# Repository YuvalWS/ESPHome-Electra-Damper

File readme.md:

# ESPHome Electra Damper

## Why?
The AC units in my rooms have electric dampers that are controlled by an IR remote. I wanted to automate them using Home Assistant.

The easy approach is to use a smart IR controller (for example, Broadlink) and record the open/close commands. This solution has some disadvantages:

1. It's less fun.
2. It requires a spot with a direct line of sight to the IR receiver.
3. It requires a permanent power source.
4. It has no feedback - if something interrupts the line of sight, I won't know whether the command worked.

## Reversing the controller
I started by disassembling the controller and examining the circuit. This is what I found.

<table>
  <tr>
    <td align="center">
      
      <div>Controller case</div>
    </td>
    <td align="center">
      
      <div>Controller front</div>
    </td>
    <td align="center">
      
      <div>Controller back</div>
    </td>
  </tr>
</table>

- It has four wires and two LEDs (green and red) that indicate state.
- The wires terminate in a **JST PH 4-pin connector (2.0 mm pitch)**, so the controller can be unplugged from the damper unit without cutting anything. Any JST PH 2.0 4-pin pigtail will mate with it.
- It has a physical toggle button, which is great because I don't have to reverse-engineer the IR protocol - I can just emulate the button press.
- I tried feeding the pictures to some AI tools, but they were not helpful and provided incorrect answers.

I didn't have enough knowledge to inspect the circuit further, so I turned to the only diagnostic tool I'm familiar with: a multimeter. I reconnected the controller and started measuring voltages.

- I identified the yellow wire as VCC (12 V) and the green wire as GND.
- There were two other wires. I assumed one was a state/input line and the other was the control line.
- The black wire measured ≈12 V at idle and dropped to ≈2.5 V when I pressed the button to open the damper, each press changes the voltage again - this is the state line.
- The red wire measured ≈5 V at idle and briefly dropped to about 1–2 V when the button was pressed. I looked this up and determined it behaves like an active-low (pull-down) control line.
### Reversing summary

| Wire   | Function                                    |
|--------|---------------------------------------------|
| Yellow | VCC (12 V)                                  |
| Green  | GND                                         |
| Black  | State (≈2.5 V when open, ≈12 V when closed) |
| Red    | Control (active-low, ≈5 V idle)             |

Connector: **JST PH 2.0 mm, 4 pins** (male header on the damper side, female housing on the controller pigtail).

## Building the smart damper
I decided to use an ESP32 board because it has a beginner-friendly workflow (ESPHome with ESPHome Builder) and an easy-to-use Home Assistant integration.
### VCC
The original controller uses a 12 V input, but ESP32 boards expect 5 V or 3.3 V. I used a DC buck converter to step the voltage down.

### State
The state voltage presented a challenge because ESP GPIO pins are limited to 3.3 V. I considered using an optocoupler to fully isolate the circuits, but I realized a 2.5 V "low" might still be enough to partially turn on an optocoupler LED, which would make detection unreliable.

Instead, I used a simple voltage divider with 10 kΩ and 3.3 kΩ resistors. This scales the ~2.5–12 V range down to roughly 0.6–3.0 V, which is safe for the ESP. This range is prefect for the default GPIO LOW\HIGH detection.

### Control
The simplest way to emulate the pull-down switch is with a transistor that connects the line to ground when activated. I used a 2N3904 NPN transistor: collector to the red wire, emitter to GND, and the base connected to a GPIO pin through a 1 kΩ resistor to protect the GPIO pin.

<div style="display: grid; grid-template-columns: minmax(auto, 800px); justify-content: center; margin: 2rem 0;">
  <figure style="margin: 0; text-align: center;">
    
    <figcaption>ESP wiring (conceptual)</figcaption>
  </figure>
</div>

## ESPHome configuration

### Project Structure
The configuration is split with ESPHome's **packages** feature, so the damper logic can be reused on any board:

```
├── common.yaml         # Shared: WiFi, API, OTA, captive portal, web server, time
├── damper_package.yaml # Damper control logic (reusable, pins via substitutions)
├── damper.yaml         # Standalone ESP32-S3 config with built-in RGB LED
├── damper_board.yaml   # ESP32-C3 SuperMini on the PCB in hardware/
├── hardware/           # PCB (Gerbers, generator script) and 3D-printed case
└── secrets.yaml        # Credentials (gitignored)
```

**Benefits:**
- Reuse the damper logic across multiple devices
- Update WiFi credentials in one place (`common.yaml`)
- Easy to create new combinations (e.g. the same damper on a different board, or with extra sensors)

### Pin Configuration
`damper_package.yaml` takes its pins from substitutions, so adapting to another ESP32 board only means changing the `substitutions` block in the device YAML:

```yaml
substitutions:
  damper_trigger_pin: "GPIO0"  # Damper control output (transistor base)
  damper_state_pin: "GPIO2"    # Damper state input (via voltage divider)

packages:
  common: !include common.yaml
  damper: !include damper_package.yaml
```

**⚠️ Strapping pins:** GPIO2 (and GPIO8/GPIO9) are strapping pins on ESP32-C3. If the board fails to boot with the damper connected, move `damper_state_pin` to a non-strapping pin (GPIO1, GPIO3, GPIO4, GPIO5, ...).

### Compiling and Flashing

**Prerequisites:**
```bash
pip install esphome
```

**Compile locally:**
```bash
esphome compile damper.yaml
```

**Flash via USB:**
```bash
esphome upload damper.yaml
```

Or manually with esptool:
```bash
esptool.py write_flash 0x0 .esphome/build/damper/.pioenvs/damper/firmware.factory.bin
```

**OTA update (after initial flash):**
```bash
esphome upload damper.yaml --device damper.local
```

Or use Home Assistant's ESPHome integration for OTA updates.

### Configuration Details
I implemented the transistor as an internal switch (no direct user control). A template button simulates the original controller's button press by turning the internal switch on for 200ms, allowing current to flow into the transistor base and actuating the pull-down. The button entity is exposed to Home Assistant to mimic the physical controller button.

A sensor reports the damper state; this is also reflected physically by the built-in RGB LED.

A template switch serves as the primary user interface for the damper. Its state is derived from the sensor so it reliably represents the actual damper position, and toggling the switch triggers the template button to change the damper state.

[Full ESPHome builder configuration yaml](damper.yaml)

<div style="display: grid; grid-template-columns: minmax(auto, 600px); justify-content: center; margin: 2rem 0;">
  <figure style="margin: 0; text-align: center;">
    
    <figcaption>Home Assistant view</figcaption>
  </figure>
</div>

## PCB and case
The perfboard prototype has a PCB and a printed wall case that can be aimed up/down and left/right in [hardware/](hardware/README.md). The board isolates the damper's wires from the ESP with optocouplers, takes a socketed ESP32-C3 SuperMini and an LD2410 presence radar, and has a jumper to choose between the damper's 12 V, an external 5 V supply, or USB. All the measurements taken on the damper's cable are recorded there.

## TODO
* Replace the ESP32-S3 with a smaller ESP module (like the ESP-Super-Mini), use a compact buck converter, and fit everything into a small tidy case. This will require using an external LED indicator instead of the ESP32-S3's built-in LED.
* Build and test the PCB in `hardware/` (designed, not yet manufactured).
* For a network-failure-proof solution, keep a physical button like the original control or add an IR receiver to support the original remote.
* I might use the fact that I already have a powered ESP32 in a strategic spot and connect additional sensors (temperature, light, or presence).

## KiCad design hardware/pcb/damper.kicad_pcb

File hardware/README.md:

# Damper controller hardware: PCB and two-axis wall case

Rev 1. A 61 x 71 mm two-layer, all through-hole board for a socketed ESP32-C3 SuperMini and an LD2410 radar, and a printed case whose wall mount aims it up/down and left/right.

Nothing here has been built yet. The board passes KiCad's design-rule check and the firmware config validates, but no board has been made, no part printed, and the two optocoupler stages have not been tried against a real damper.

## Do not order before these checks

| # | Check | Why |
|---|-------|-----|
| 1 | Build the control and state stages (see Circuit) on a breadboard and try them on the damper | They replace the divider and bare transistor that are known to work. Component values come from the measurements below, not from a test. |
| 2 | Print `pcb/damper-1to1.pdf` at 100 % and press the real SuperMini, LD2410, JST header, regulator and screw terminal onto the paper | Footprints come from KiCad's library and from caliper photos, not from parts in hand. |
| 3 | Read the pin names printed on your LD2410C and compare with J7: TX, RX, OUT, GND, VCC from the top | The order matches Hi-Link's data sheet (V1.00, table 1), but clones differ. If it is reversed the module still fits: it then lies to the other side of J7. If it is different, edit `RADAR_C` in `pcb/gen_pcb.py`. |
| 4 | With the board bare, plug the wall cable into J1 and confirm yellow lands on the pin marked Y | Yellow = pin 1 was read from a photo of the original board. |
| 5 | Measure the height of the SuperMini's USB-C socket above the PCB once it sits in its sockets | `usb_z` and `stack_h` in `case/case.scad` assume 13.6 mm and 18 mm. |

## Review, 19 November 2026

An outside review of this branch raised three points. Results of checking each:

| Point | Result |
|-------|--------|
| The board file at commit `ba88094` has three copper defects (a CTRL track through pad D3.2, pad JP2.2 cut off from GND, JP2.2 overlapping D2.1) and the Gerber ZIP is an older layout | Not a fault in the board; it is how the review read the file. The review's file hashes match `ba88094`, and the ZIP's copper, mask, silkscreen, outline and drill files are identical to a fresh KiCad export of that same file. All three defects sit on D3 and JP2, the only footprints turned 90 degrees, and they reproduce exactly when the 90-degree rotation is applied with the wrong sign: KiCad's y axis points down, so the y-up rotation formula mirrors the pads. With that error, D3.2 lands 0.254 mm from the CTRL track (the review's own figure; it is really 6.35 mm away), and JP2.2 lands 1.8 mm from D2.1, inside the damper-side pour. KiCad's design-rule check finds no shorts or unconnected nets, and a separate script that tests every pad against every pad and track of another net finds no conflicts. Regenerating from `gen_pcb.py` is safe; tools that read `.kicad_pcb` files directly must apply footprint rotation clockwise. |
| The radar is fed through D1, below its advised 5 V | Confirmed and fixed. D1 now feeds only the ESP's 5V pin; the radar sits on the rail ahead of it (see Power select). |
| The 200 mA isolated converter U4 cannot supply the radar | Confirmed. Hi-Link asks for more than 200 mA of supply capacity for the LD2410C. U4 is now marked for boards without the radar. |

## Measurements

Taken on the wall cable with the original controller unplugged, unless noted. Same results in two rooms.

### Connector

JST PH, 2.0 mm pitch, 4 positions. Female housing on the wall cable, male header on the controller.

| Pin | Wire | Function |
|-----|------|----------|
| 1 | Yellow | 12 V |
| 2 | Green | GND |
| 3 | Red | Control, pulled low to toggle |
| 4 | Black | State |

Order as seen with the housing's key facing you, left to right: yellow, green, red, black. On the original board yellow sits on the square pad. A bought JST PH pigtail may use other colours (the one used for measuring has white in place of green).

### Voltages

| Line | Condition | Open circuit | With 10 k to GND |
|------|-----------|--------------|------------------|
| Red (control) | idle | 5.15 V | 5.10 V |
| Black (state) | damper closed | 12.07 V | 11.95 V |
| Black (state) | damper open | 0 V | 0 V |
| Black (state) | damper open, original controller connected | 2.5 V | - |
| Yellow (12 V) | no load | 12.09 V | 11.97 V |
| Yellow (12 V) | powering the ESP32-S3 (N16R8 dev board) through a buck converter | 11.55 V | - |

What they say:

- **Control** has about 100 ohm behind it, so pulling it low takes tens of mA. The original button pulls it to 1-2 V, not to 0.
- **State** is stiff at 12 V when closed. When open it reads 0 V on a bare cable and 2.5 V with the original controller attached, so the 2.5 V comes from the controller's own circuit. The detector's threshold of about 6 V handles both.
- **12 V** drops 0.54 V under an ESP32-S3. It can power the board, but there is not much to spare.

Short-circuit currents were also read with the meter on its 20 mA range: red to green 0, black to green 0, yellow to green 0.83 mA. They contradict the voltage readings above and are not used. Do not repeat them: shorting the 12 V line through a meter is a dead short.

### Parts

| Part | Measured |
|------|----------|
| ESP32-C3 SuperMini (HW-466AB) | about 18 x 22.5 mm, two rows of 8 pins |
| HLK-LD2410C V1.1 | about 16 mm across the edge with the 5-pin 2.54 mm header |
| HLK-LD2410B | about 7 mm wide, five 1.27 mm pads on one short end |

Read from caliper photos, good to about half a millimetre.

## Files

| File | What it is |
|------|------------|
| `pcb/gerbers/damper-rev1.zip` | Gerbers and drill files. Upload to PCBWay: 2 layers, 1.6 mm, any colour, lead-free HASL. `source.txt` inside records the SHA-256 of the `damper.kicad_pcb` they were exported from. |
| `pcb/damper.kicad_pcb` | The board, opens in KiCad 9 or newer. |
| `pcb/gen_pcb.py` | Generates the board. There is no schematic; the netlist is the part tables in this script, and it routes the tracks itself. |
| `pcb/export.ps1` | Runs the generator, the design-rule check, and writes the Gerbers and the PDF. |
| `pcb/damper-1to1.pdf` | Pads, silkscreen and outline at 1:1 for the paper check. |
| `pcb/bom.csv` | Parts list, written by the generator. |
| `case/case.scad` | Parametric case (OpenSCAD). |
| `case/body.stl`, `cover.stl`, `swing-plate.stl`, `wall-plate.stl` | Printable parts, already in print orientation. |
| `case/case-ball.scad` | The same case on a ball-joint mount. Includes `case.scad`. |
| `case/body-ball.stl`, `cover-ball.stl`, `ball-stalk.stl`, `ball-base.stl`, `tripod-adapter.stl` | Printable parts for the ball-joint version. |
| `../damper_board.yaml` | ESPHome config for this board. |

After editing `gen_pcb.py`:

```
pwsh hardware/pcb/export.ps1
```

The design-rule check in that script ignores courtyard overlaps: the axial resistors sit on a 2.54 mm pitch, closer than KiCad's courtyards allow, which is tight but fits 1/4 W parts.

## Circuit

Two grounds: `AC_GND` on the damper side (bottom-left block of the board, outlined on the silkscreen) and `GND` on the ESP side. Only U1, U2, the regulator and the jumper JP2 cross the 1 mm gap between them.

```
 DAMPER SIDE (AC_GND)                    |  ESP SIDE (GND)
                                         |
 12V --F1 PTC--D2 1N5819--+--C1 100uF    |
                 D3 TVS 15V to AC_GND    |
                          +--> U3 or U4 --> 5V_REG
                                         |
 12V --R5 4k7--> U1 collector            |  GPIO0 --R1 220R--> U1 LED --> GND
 U1 emitter --+-- Q2 base, R6 10k to AC_GND
 CTRL (red) --R7 33R-- Q2 collector      |
              Q2 emitter -> AC_GND       |
                                         |
 STATE (black) --ZD1 5V1--R8 10k--+-- Q1 base, R9 10k to AC_GND
 12V --R10 2k2--> U2 LED --> Q1 collector|  3V3 --R2 10k--+-- GPIO1
                  Q1 emitter -> AC_GND   |                U2 collector, emitter GND
```

- **Control:** the optocoupler U1 turns on Q2, which pulls the red wire down through R7. 33 ohm limits the current to about 40 mA and leaves the line near 1.3 V, like the original button. If the damper does not react, replace R7 with a wire link; that is what the prototype's transistor does.
- **State:** the zener sets a threshold near 6 V. Below it Q1 is off; at 12 V Q1 lights U2's LED from the 12 V rail. The state wire itself supplies only about 0.6 mA, less than the prototype's divider.
- **Logic:** a closed damper reads low on GPIO1, an open one high. An unplugged cable reads "open". This is the opposite of the prototype, hence `damper_state_inverted: "false"` in `damper_board.yaml`.
- **12 V input:** resettable fuse F1, reverse-polarity diode D2, TVS diode D3.

### 12 V to 5 V: fit U3 or U4, never both

| Fit | Part | JP2 "GND LINK" | Result |
|-----|------|----------------|--------|
| U3 (recommended) | K7805-1000R3 or R-78E5.0-1.0, fixed 5 V switching regulator | on | Same arrangement as the working prototype. The grounds are joined; the control and state wires are still buffered by the optocouplers. |
| U4 | B1205S-1W, isolated 12 V to 5 V, SIP-4 | off | The two sides share no conductor. **Not with the radar:** it delivers 200 mA, and Hi-Link asks for a supply that can deliver more than 200 mA for the LD2410C alone, before the ESP's Wi-Fi peaks. It also wants 10.8-13.2 V in, while the line was measured at 11.55 V under a comparable load. Use it only on a board without the radar. |

The U4 footprint is four pads on a 2.54 mm pitch in the order -Vin, +Vin, -Vout, +Vout. Check the datasheet of the part you buy.

With U3 fitted, pulling JP2 while powering from USB or from J2 isolates the ESP from the damper completely.

### Is the damper's 12 V safe to use as the power input?

Yes, under these conditions. The only evidence about the supply is the measurements above: its rating is not known.

- **Fit U3, with JP2 on.** This is the arrangement the prototype runs on. U4 is the risky choice: it wants at least 10.8 V in, the line was measured at 11.55 V under load, and its 200 mA is too little for the radar.
- **Keep the load small.** The ESP32-C3, the radar and the three LEDs are about the same load as the prototype's ESP32-S3, which pulled the line down by 0.54 V. Do not hang LED strips, relays or servos on the 5 V rail.
- **Check once on the finished board.** With everything running and Wi-Fi active, yellow to green should stay above about 11 V, and the damper should still open and close normally.
- **Faults are covered on the board.** A short trips the resettable fuse F1 at 500 mA; a reversed plug is blocked by D2; a voltage spike is clamped by D3.
- **USB and 12 V together are fine** as long as D1 is fitted: it stops USB feeding back into the rail, the regulator and the damper.
- **Flashing from a mains-powered PC:** with JP2 on, the PC's ground is joined to the damper's ground through the USB cable. That is normally harmless. To rule it out, pull JP2 first; the optocouplers keep the damper control working without it.

### Power select, JP1

| Jumper | Source |
|--------|--------|
| `AC` (top two pins) | 5 V from U3/U4, fed by the damper's 12 V |
| `EXT` (bottom two pins) | 5 V from the screw terminal J2 |
| parked on JP3 | none: USB-C on the ESP |

The jumper's middle pin is the 5 V rail. The radar (J7, J8), J11 and the bulk capacitors C2-C4 sit on it directly, so the radar gets the regulator's full 5 V; Hi-Link rates its VCC at 5-12 V, 5 V advised.

D1 (1N5817) feeds the ESP's 5V pin from the rail and blocks the other way, so a USB cable cannot feed back into the rail, the regulator or J2. The ESP gets about 4.7 V, which its own 3.3 V regulator handles. Do not replace D1 with a wire link.

With the jumper parked, only USB powers the board: the ESP runs, the rail and the radar are off. To try the radar on the bench, put the jumper on `EXT` and feed 5 V into J2; USB can stay plugged in.

### ESP32-C3 SuperMini

Plugs into two 1x8 sockets (J3, J4), USB-C towards the bottom edge. There is no copper under its antenna.

| GPIO | Use |
|------|-----|
| 0 | Damper trigger |
| 1 | Damper state |
| 6, 7 | Green, red LED: damper open / closed |
| 10 | Blue LED: for Home Assistant to drive, for example the AC's state |
| 20, 21 | Radar UART (ESP RX, ESP TX) |
| 3 | Radar OUT, also on the AUX header |
| 4, 5 | I2C header (SDA, SCL) |
| 2, 8, 9 | Free. 2, 8 and 9 are strapping pins; 8 is the onboard LED, 9 the BOOT button |

### Spare holes

- **J5, J6:** the ESP's pins, 1:1, beside each socket. 5V and GND are not in J5 (the screw terminal is in the way); take them from J11.
- **J9 I2C:** 3V3, GND, SDA (GPIO4), SCL (GPIO5).
- **J10 AUX:** 3V3, GND, GPIO3. For an IR receiver or a button.
- **J11:** 5 V rail, GND. Unpowered while the jumper is parked.
- **J1B:** the four damper wires again on a 2.54 mm pitch, for a soldered pigtail in place of the JST header.
- **PROTO:** twelve unconnected pads.

### Radar

- **LD2410C:** solder its pin header so the antenna side faces away from the board, and plug it into J7. It lies flat, to the left or to the right of J7 depending on which end its pin 1 is. Both areas are kept free of tall parts; the parts underneath are lower than the socket.
- **LD2410B:** J8 has its five signals on a 1.27 mm pitch (OUT, TX, RX, GND, VCC from the top). Wire it with a short cable, or stand it on a 1.27 mm header.

Solder the three LEDs standing tall, so their domes reach the holes in the cover.

## Case

About 69 x 79 mm and 28 mm deep; the wall plate is 101 x 56 mm and the mount adds 10 mm behind the case. PLA or PETG, 0.2 mm layers, no supports. Hardware: four M3 x 20 screws with nuts, four M3 x 6, two wall screws.

The mount has two axes, so the radar can look across a room from an upper corner:

- **Wall plate:** two screws into the wall, 48 mm apart, heads sunk into the plate. The wall cable comes through the opening in the middle. It has hinge lugs on both side edges.
- **Swing plate, left/right:** sits on the wall plate and opens like a door, 0 to 90 degrees. Fit two M3 x 20 screws and nuts on **one** side only: hinge it on the side that faces the room, so the edge nearest the corner swings away from the wall. The nuts sit in the hex pockets on the inner ends of the swing plate's knuckles. The upper screw goes in from above, so set its friction before hanging the unit near a ceiling; the lower one stays reachable from below.
- **Tilt hinge, up/down:** an M3 x 20 screw and nut on each side, through the swing plate's lug into the body's knuckle; the nut sits in the hex pocket on the knuckle's inner end. Tilt the case forward until the radar looks where you want, then tighten. Flat is 0 degrees; about 45 degrees is the useful limit. To tilt upward instead, mount everything upside down.
- **Order of assembly:** join the two plates with the pan screws, screw the wall plate to the wall through the two access holes in the swing plate, then hang the body on the tilt screws.
- **Body:** the PCB sits on four posts, M3 x 6 screws. Without the mount, the body hangs flat on two screws through the keyholes in its back.
- **Cover:** snaps over the body's lip. The bottom wall has one wide notch for the JST plug and the 5 V cable, open towards the rim so the cover goes on with cables plugged, and a window for USB-C. Three holes for the LEDs, and a thinner patch over the SuperMini so its own LED glows through. The face over the radar is closed, 1.2 mm thick.

Not checked on real hardware: the snap fit (`snap`, `lip_gap`), whether the two hinges hold their angles by friction alone, and the USB window height. The model was checked for collisions between the mount and the case over the whole pan and tilt range (`part="clash"` in `case.scad` must render empty). Expect one test print.

### Alternative: ball-joint mount

`case/case-ball.scad` is the same body and cover without the hinge, on a ball-and-socket mount, for aiming in one smooth movement. Print `body-ball.stl` and `cover-ball.stl` instead of `body.stl` and `cover.stl`; the two mounts do not mix.

- **Base (`ball-base.stl`):** a 64 mm disc with two wall screws 48 mm apart and an opening for the wall cable. The socket is split and closed by an M3 x 16 screw and nut underneath: loosen, aim, tighten.
- **Stalk (`ball-stalk.stl`):** a 22 mm ball on a neck that flares into a flange. Four countersunk M3 x 8 screws go through the back of the body, from the inside, into the flange. Drive an M3 x 30 screw down the middle of the stalk from the flange end before fitting it: the printed neck is weakest across its layers, and the screw is what keeps it from snapping.
- **Reach:** about 50 degrees from straight out, in any direction. 45 degrees sideways combined with 30 degrees down is just inside that.
- **Depth:** the case stands off the wall like a small camera: its back is 55 mm from the wall, its face about 83 mm. It needs that room so the edges clear the wall when it is aimed.
- **Order of assembly:** screw the base to the wall first, because the case covers the wall screws afterwards. Then, with the clamp screw loose, press the ball in; it snaps past the socket's rim.

A printed ball joint holds this case (it weighs little) but it does not feel like a bought one: the layer lines make the movement slightly notchy, and PLA under a clamp relaxes over months, so expect to retighten. PETG is the better material for the base. Sand the ball lightly if it grates.

For a smoother joint, buy a mini camera ball head or a small security-camera wall mount with a 1/4"-20 thread, and print `tripod-adapter.stl` instead of the base and stalk. The adapter holds a 1/4"-20 nut against the back of the body and is fixed by the same four M3 x 8 screws.

Not checked on real hardware: the socket fit (`ball_clr`), how hard the clamp grips, and the nut pocket of the adapter. The model was checked for collisions the same way as the hinge mount (`part="ball_clash"`).

## Firmware

`damper_board.yaml` in the repository root. It validates with `esphome config`; it has not been compiled or flashed.

The radar package (`presence_package.yaml`) is on the `feature/presence-sensor` branch. Once that is merged, uncomment the `presence:` line in `damper_board.yaml`; the UART pins are already set.

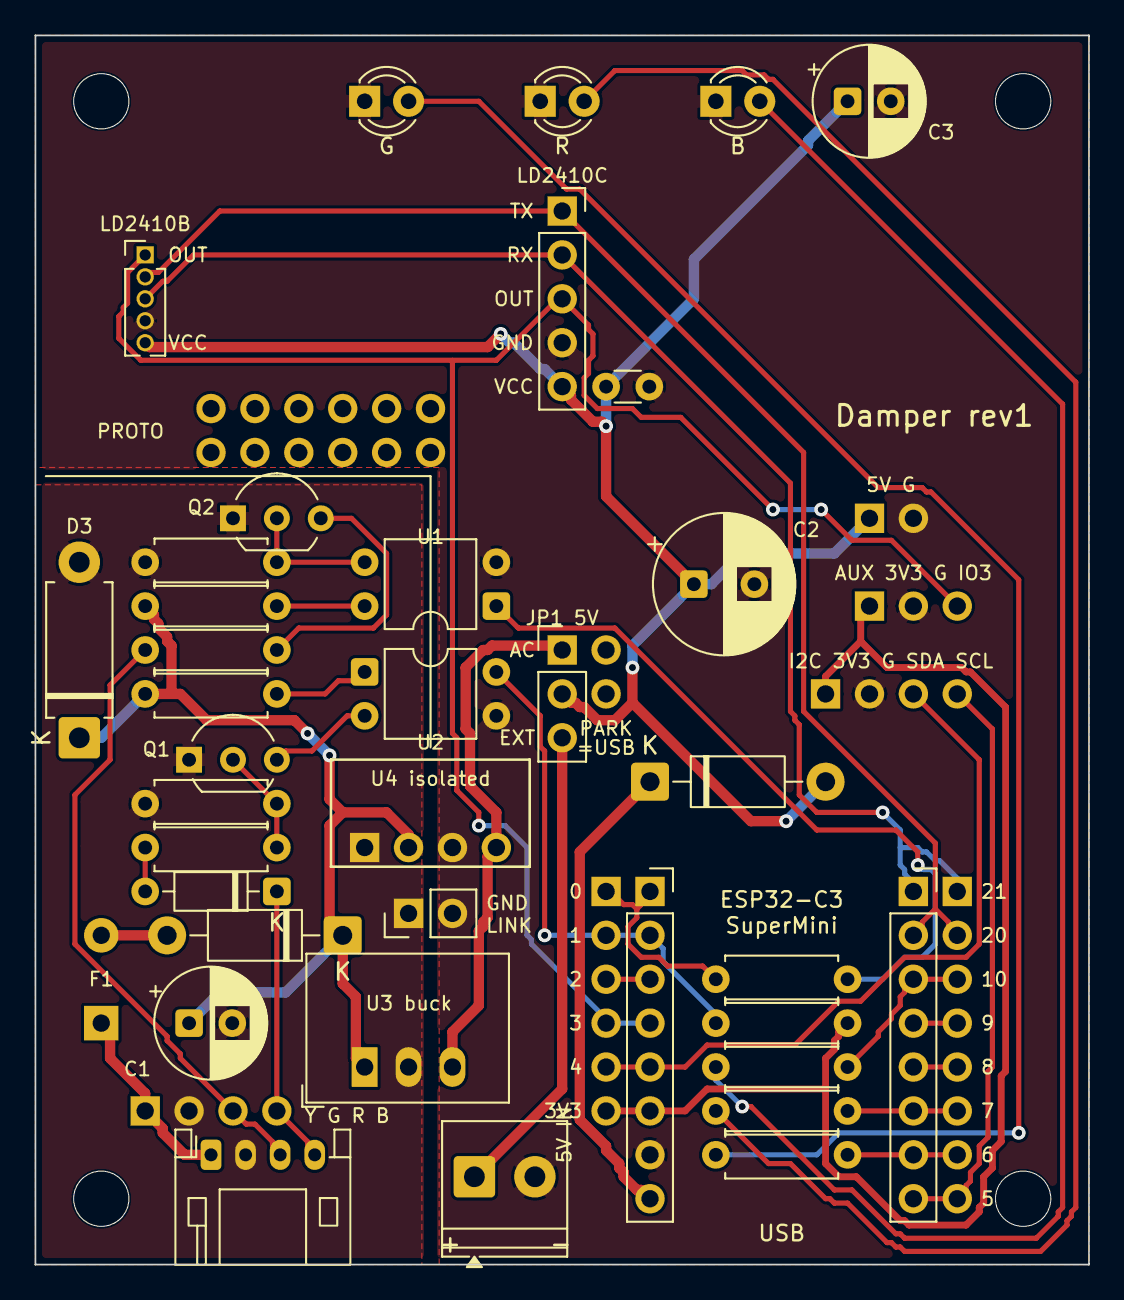
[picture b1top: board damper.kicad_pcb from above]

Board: 2 copper layers, 61.0 x 71.1 mm, 49 parts (0 on the bottom side), 36 nets.

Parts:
C1: 100uF 25V; CP_Radial_D6.3mm_P2.50mm
C2: 470uF 10V; CP_Radial_D8.0mm_P3.50mm
C3: 100uF 10V; CP_Radial_D6.3mm_P2.50mm
C4: 100nF; C_Disc_D3.0mm_W1.6mm_P2.50mm
D1: 1N5817; D_DO-41_SOD81_P10.16mm_Horizontal
D2: 1N5819; D_DO-41_SOD81_P10.16mm_Horizontal
D3: P6KE15A; D_DO-15_P10.16mm_Horizontal
D4: LED 3mm green; LED_D3.0mm
D5: LED 3mm red; LED_D3.0mm
D6: LED 3mm blue; LED_D3.0mm
F1: PTC 500mA
H1, H2, H3, H4: M3
J1: JST S4B-PH-K; JST_PH_S4B-PH-K_1x04_P2.00mm_Horizontal
J1B: pigtail pads
J2: 5V in; TerminalBlock_Phoenix_PT-1,5-2-3.5-H_1x02_P3.50mm_Horizontal
J3, J4: socket 1x8; PinSocket_1x08_P2.54mm_Vertical
J5, J6: breakout
J7: socket 1x5; PinSocket_1x05_P2.54mm_Vertical
J8: header 1x5 1.27mm; PinHeader_1x05_P1.27mm_Vertical
J9: I2C
J10: AUX
J11: 5V out
JP1: power select; PinHeader_1x03_P2.54mm_Vertical
JP2: GND link; PinHeader_1x02_P2.54mm_Vertical
JP3: jumper park
PROTO: prototyping pads
Q1, Q2: 2N3904; TO-92_Inline_Wide
R1: 220R; R_Axial_DIN0207_L6.3mm_D2.5mm_P7.62mm_Horizontal
R2, R6, R8, R9: 10k; R_Axial_DIN0207_L6.3mm_D2.5mm_P7.62mm_Horizontal
R5: 4k7; R_Axial_DIN0207_L6.3mm_D2.5mm_P7.62mm_Horizontal
R7: 33R; R_Axial_DIN0207_L6.3mm_D2.5mm_P7.62mm_Horizontal
R10: 2k2; R_Axial_DIN0207_L6.3mm_D2.5mm_P7.62mm_Horizontal
R11, R12, R13: 330R; R_Axial_DIN0207_L6.3mm_D2.5mm_P7.62mm_Horizontal
U1, U2: PC817C; DIP-4_W7.62mm
U3: K7805-1000R3; Converter_DCDC_RECOM_R-78E-0.5_THT
U4: B1205S-1W
ZD1: 5V1 zener 0.5W; D_DO-35_SOD27_P7.62mm_Horizontal

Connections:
5V_ESP: D1.1, J3.8
5V_EXT: J2.1, JP1.3
5V_REG: JP1.1, U3.3, U4.4
12V_F: D2.2, F1.2
12V_IN: F1.1, J1.1, J1B.1
12V_P: C1.1, D2.1, D3.1, R5.1, R10.1, U3.1, U4.2
+3V3: J3.6, J5.6, J9.1, J10.1, R2.2
+5V: C2.1, C3.1, C4.1, D1.2, J7.5, J8.5, J11.1, JP1.2
AC_GND: C1.2, D3.2, J1.2, J1B.2, JP2.1, Q1.1, Q2.1, R6.1, R9.1, U3.2, U4.1
CTRL: J1.3, J1B.3, R7.1
CTRL_Q: Q2.3, R7.2
GND: C2.2, C3.2, C4.2, D4.1, D5.1, D6.1, J2.2, J3.7, J7.4, J8.4, J9.2, J10.2, J11.2, JP2.2, U1.2, U2.3, U4.3
IO0: J3.1, J5.1, R1.1
IO1: J3.2, J5.2, R2.1, U2.4
IO2: J3.3, J5.3
IO3: J3.4, J5.4, J7.3, J8.1, J10.3
IO4: J3.5, J5.5, J9.3
IO5: J4.8, J6.8, J9.4
IO6: J4.7, J6.7, R11.2
IO7: J4.6, J6.6, R12.2
IO8: J4.5, J6.5
IO9: J4.4, J6.4
IO10: J4.3, J6.3, R13.2
IO20: J4.2, J6.2, J7.1, J8.2
IO21: J4.1, J6.1, J7.2, J8.3
LED_B: D6.2, R13.1
LED_G: D4.2, R11.1
LED_R: D5.2, R12.1
Q1_B: Q1.2, R8.2, R9.2
Q1_C: Q1.3, U2.2
Q2_B: Q2.2, R6.2, U1.3
STATE: J1.4, J1B.4, ZD1.1
ST_Z: R8.1, ZD1.2
U1_A: R1.2, U1.1
U1_C: R5.2, U1.4
U2_A: R10.2, U2.1

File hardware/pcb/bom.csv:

Ref,Value,Footprint,Note
C1,100uF 25V,CP_Radial_D6.3mm_P2.50mm,
C2,470uF 10V,CP_Radial_D8.0mm_P3.50mm,
C3,100uF 10V,CP_Radial_D6.3mm_P2.50mm,
C4,100nF,C_Disc_D3.0mm_W1.6mm_P2.50mm,
D1,1N5817,D_DO-41_SOD81_P10.16mm_Horizontal,rail to the ESP's 5V pin; blocks USB back-feed
D2,1N5819,D_DO-41_SOD81_P10.16mm_Horizontal,reverse polarity
D3,P6KE15A,D_DO-15_P10.16mm_Horizontal,TVS
D4,LED 3mm green,LED_D3.0mm,
D5,LED 3mm red,LED_D3.0mm,
D6,LED 3mm blue,LED_D3.0mm,
F1,PTC 500mA,,"resettable fuse, 5 mm pitch, e.g. RXEF050"
J1,JST S4B-PH-K,JST_PH_S4B-PH-K_1x04_P2.00mm_Horizontal,"side entry, mates with the wall cable"
J2,5V in,"TerminalBlock_Phoenix_PT-1,5-2-3.5-H_1x02_P3.50mm_Horizontal",3.5 mm screw terminal
J3,socket 1x8,PinSocket_1x08_P2.54mm_Vertical,for the ESP32-C3 SuperMini
J4,socket 1x8,PinSocket_1x08_P2.54mm_Vertical,for the ESP32-C3 SuperMini
J7,socket 1x5,PinSocket_1x05_P2.54mm_Vertical,for LD2410C
J8,header 1x5 1.27mm,PinHeader_1x05_P1.27mm_Vertical,optional: for LD2410B
JP1,power select,PinHeader_1x03_P2.54mm_Vertical,3-pin header + jumper
JP2,GND link,PinHeader_1x02_P2.54mm_Vertical,2-pin header + jumper
JP3,jumper park,,"2-pin header, optional"
Q1,2N3904,TO-92_Inline_Wide,E B C
Q2,2N3904,TO-92_Inline_Wide,E B C
R1,220R,R_Axial_DIN0207_L6.3mm_D2.5mm_P7.62mm_Horizontal,U1 LED current
R2,10k,R_Axial_DIN0207_L6.3mm_D2.5mm_P7.62mm_Horizontal,state pull-up
R5,4k7,R_Axial_DIN0207_L6.3mm_D2.5mm_P7.62mm_Horizontal,
R6,10k,R_Axial_DIN0207_L6.3mm_D2.5mm_P7.62mm_Horizontal,
R7,33R,R_Axial_DIN0207_L6.3mm_D2.5mm_P7.62mm_Horizontal,wire link if the damper does not react
R8,10k,R_Axial_DIN0207_L6.3mm_D2.5mm_P7.62mm_Horizontal,
R9,10k,R_Axial_DIN0207_L6.3mm_D2.5mm_P7.62mm_Horizontal,
R10,2k2,R_Axial_DIN0207_L6.3mm_D2.5mm_P7.62mm_Horizontal,
R11,330R,R_Axial_DIN0207_L6.3mm_D2.5mm_P7.62mm_Horizontal,green LED
R12,330R,R_Axial_DIN0207_L6.3mm_D2.5mm_P7.62mm_Horizontal,red LED
R13,330R,R_Axial_DIN0207_L6.3mm_D2.5mm_P7.62mm_Horizontal,blue LED
U1,PC817C,DIP-4_W7.62mm,control optocoupler
U2,PC817C,DIP-4_W7.62mm,state optocoupler
U3,K7805-1000R3,Converter_DCDC_RECOM_R-78E-0.5_THT,or R-78E5.0-1.0; needs JP2 closed
U4,B1205S-1W,,"optional, NOT with the radar (200 mA): isolated SIP-4 (-Vin +Vin -Vo +Vo), INSTEAD of U3, JP2 open"
ZD1,5V1 zener 0.5W,D_DO-35_SOD27_P7.62mm_Horizontal,BZX55C5V1
-,ESP32-C3 SuperMini,,plugs into J3/J4
-,HLK-LD2410C (or LD2410B),,plugs into J7 (or wired to J8)
-,jumper 2.54 mm x2,,"JP1, JP2"
